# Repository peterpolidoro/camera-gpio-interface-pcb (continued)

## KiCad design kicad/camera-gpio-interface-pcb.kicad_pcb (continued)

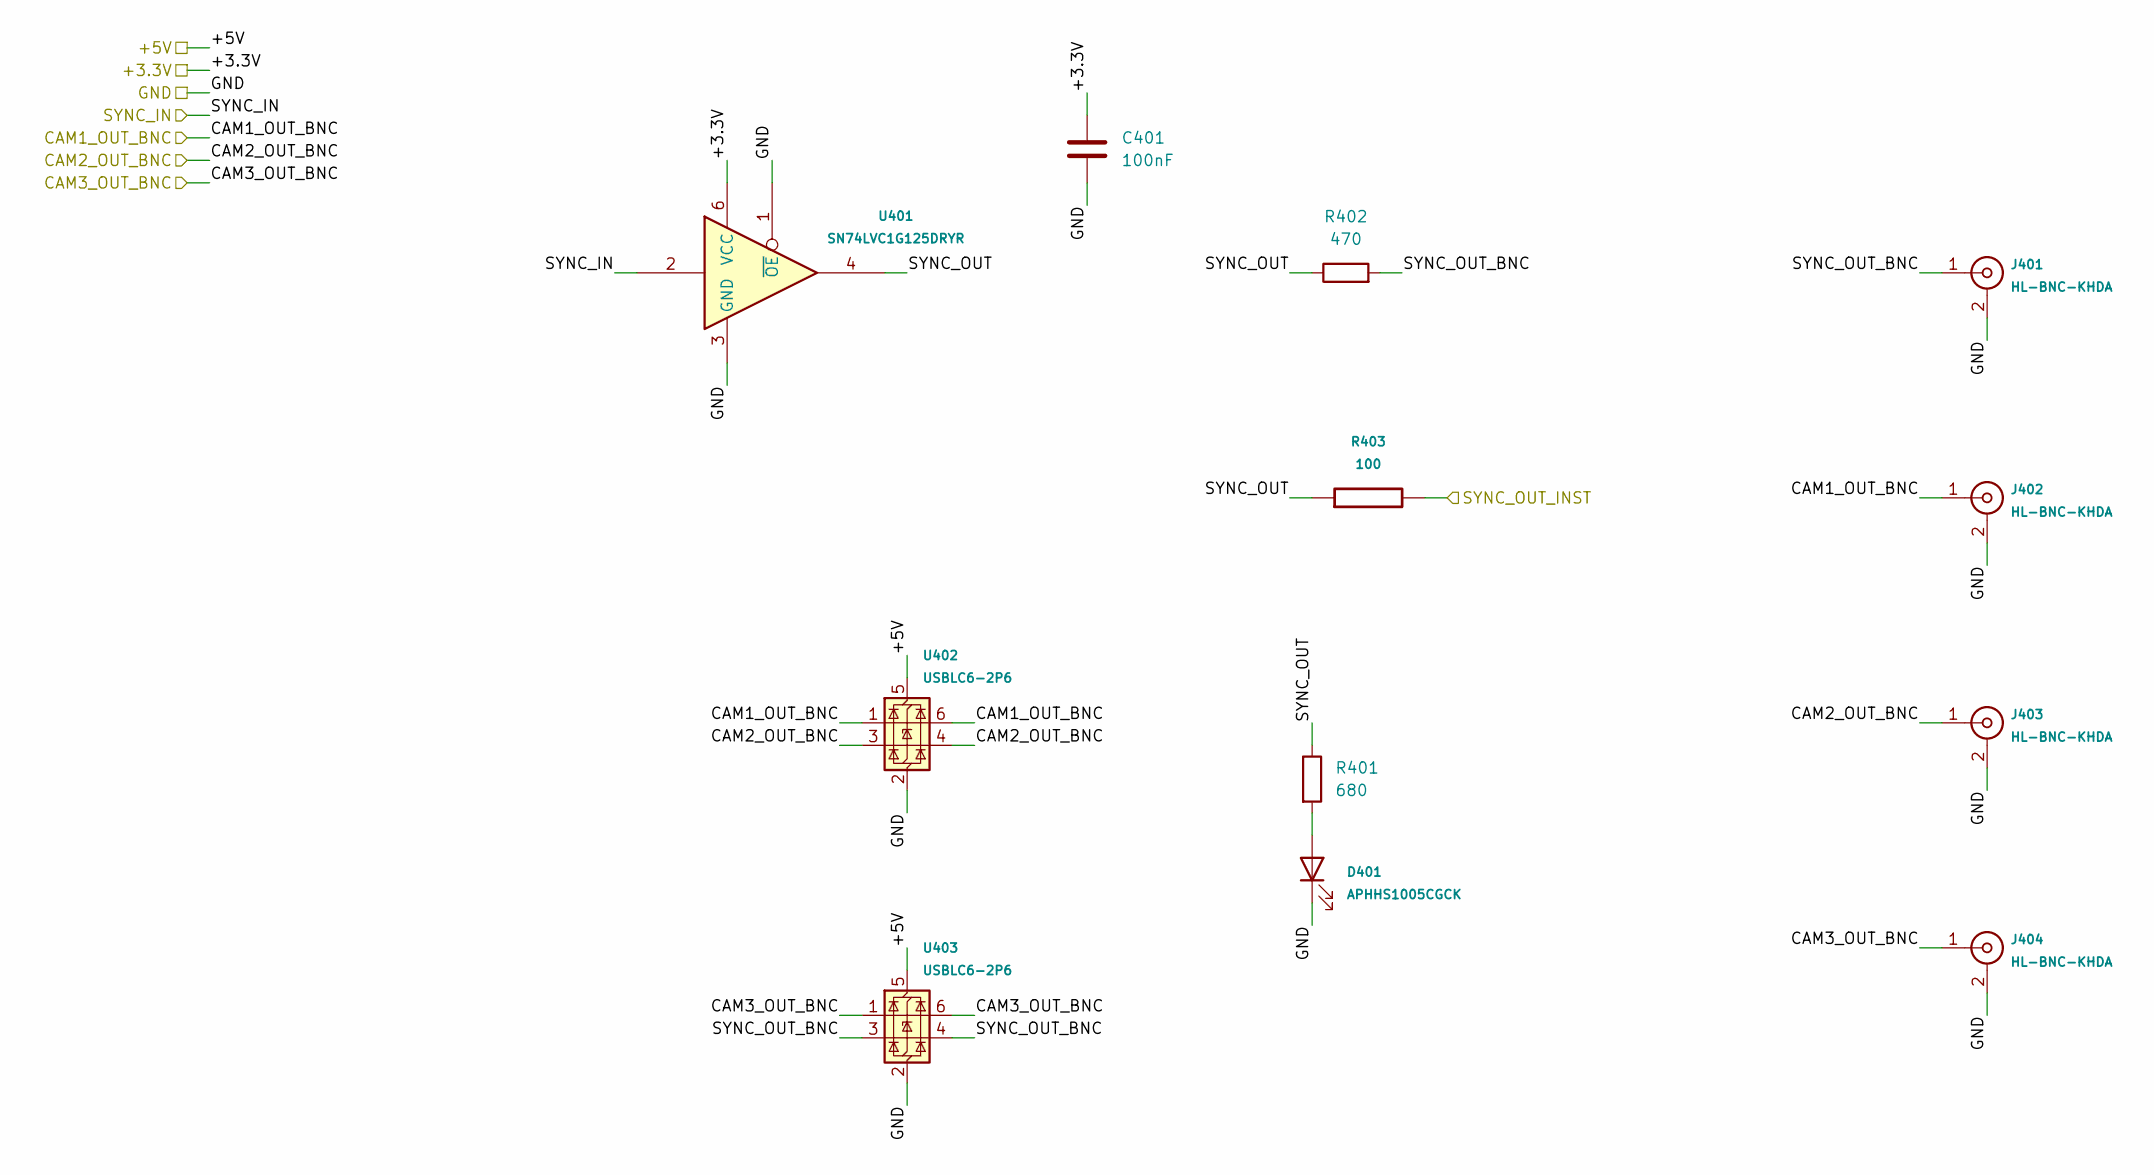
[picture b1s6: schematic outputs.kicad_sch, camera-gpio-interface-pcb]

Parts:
C401: 100nF; C_0402_1005Metric; PartID sym_orb_weaver_passives_c_0_1uf_100v_04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
D401: APHHS1005CGCK; LED_0402-1005_KNB; PartID sym_orb_weaver_misc_led_knb_20ma_grn_2_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
J401, J402, J403, J404: HL-BNC-KHDA; CONN_BNC_HL-BNC-KHDA; PartID sym_orb_weaver_connectors_conn_coaxial_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
R401: 680; R_0402_1005Metric; PartID mpn_rc0402fr_07680rl_0402
R402: 470; R_0603_1608Metric; PartID mpn_0603waf4700t5e_0603
R403: 100; R_0402_1005Metric; PartID sym_orb_weaver_passives_r_100_0402
U401: SN74LVC1G125DRYR; DRY6; PartID sym_orb_weaver_misc_buffer_74lvc1g125dr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
U402, U403: USBLC6-2P6; USBLC6-2P6_SOT-666; PartID mpn_usblc6_2p6_sot_666_6

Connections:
/+3.3V: C401.1, U401.6 (VCC); also elsewhere on the board
/+5V: U402.5 (VBUS), U403.5 (VBUS); also elsewhere on the board
/CAM1_OUT_BNC: J402.1 (Signal), U402.1 (I/O1), U402.6 (I/O1); also elsewhere on the board
/CAM2_OUT_BNC: J403.1 (Signal), U402.3 (I/O2), U402.4 (I/O2); also elsewhere on the board
/CAM3_OUT_BNC: J404.1 (Signal), U403.1 (I/O1), U403.6 (I/O1); also elsewhere on the board
/GND: C401.2, D401.1 (K), J401.2 (Shield), J402.2 (Shield), J403.2 (Shield), J404.2 (Shield), U401.1 (~OE), U401.3 (GND), U402.2 (GND), U403.2 (GND); also elsewhere on the board
/SYNC_IN: U401.2; also elsewhere on the board
/SYNC_OUT_INST: R403.2; also elsewhere on the board
/outputs/SYNC_OUT: R401.1, R402.1, R403.1, U401.4
/outputs/SYNC_OUT_BNC: J401.1 (Signal), R402.2, U403.3 (I/O2), U403.4 (I/O2)
unnamed: D401.2 (A), R401.2

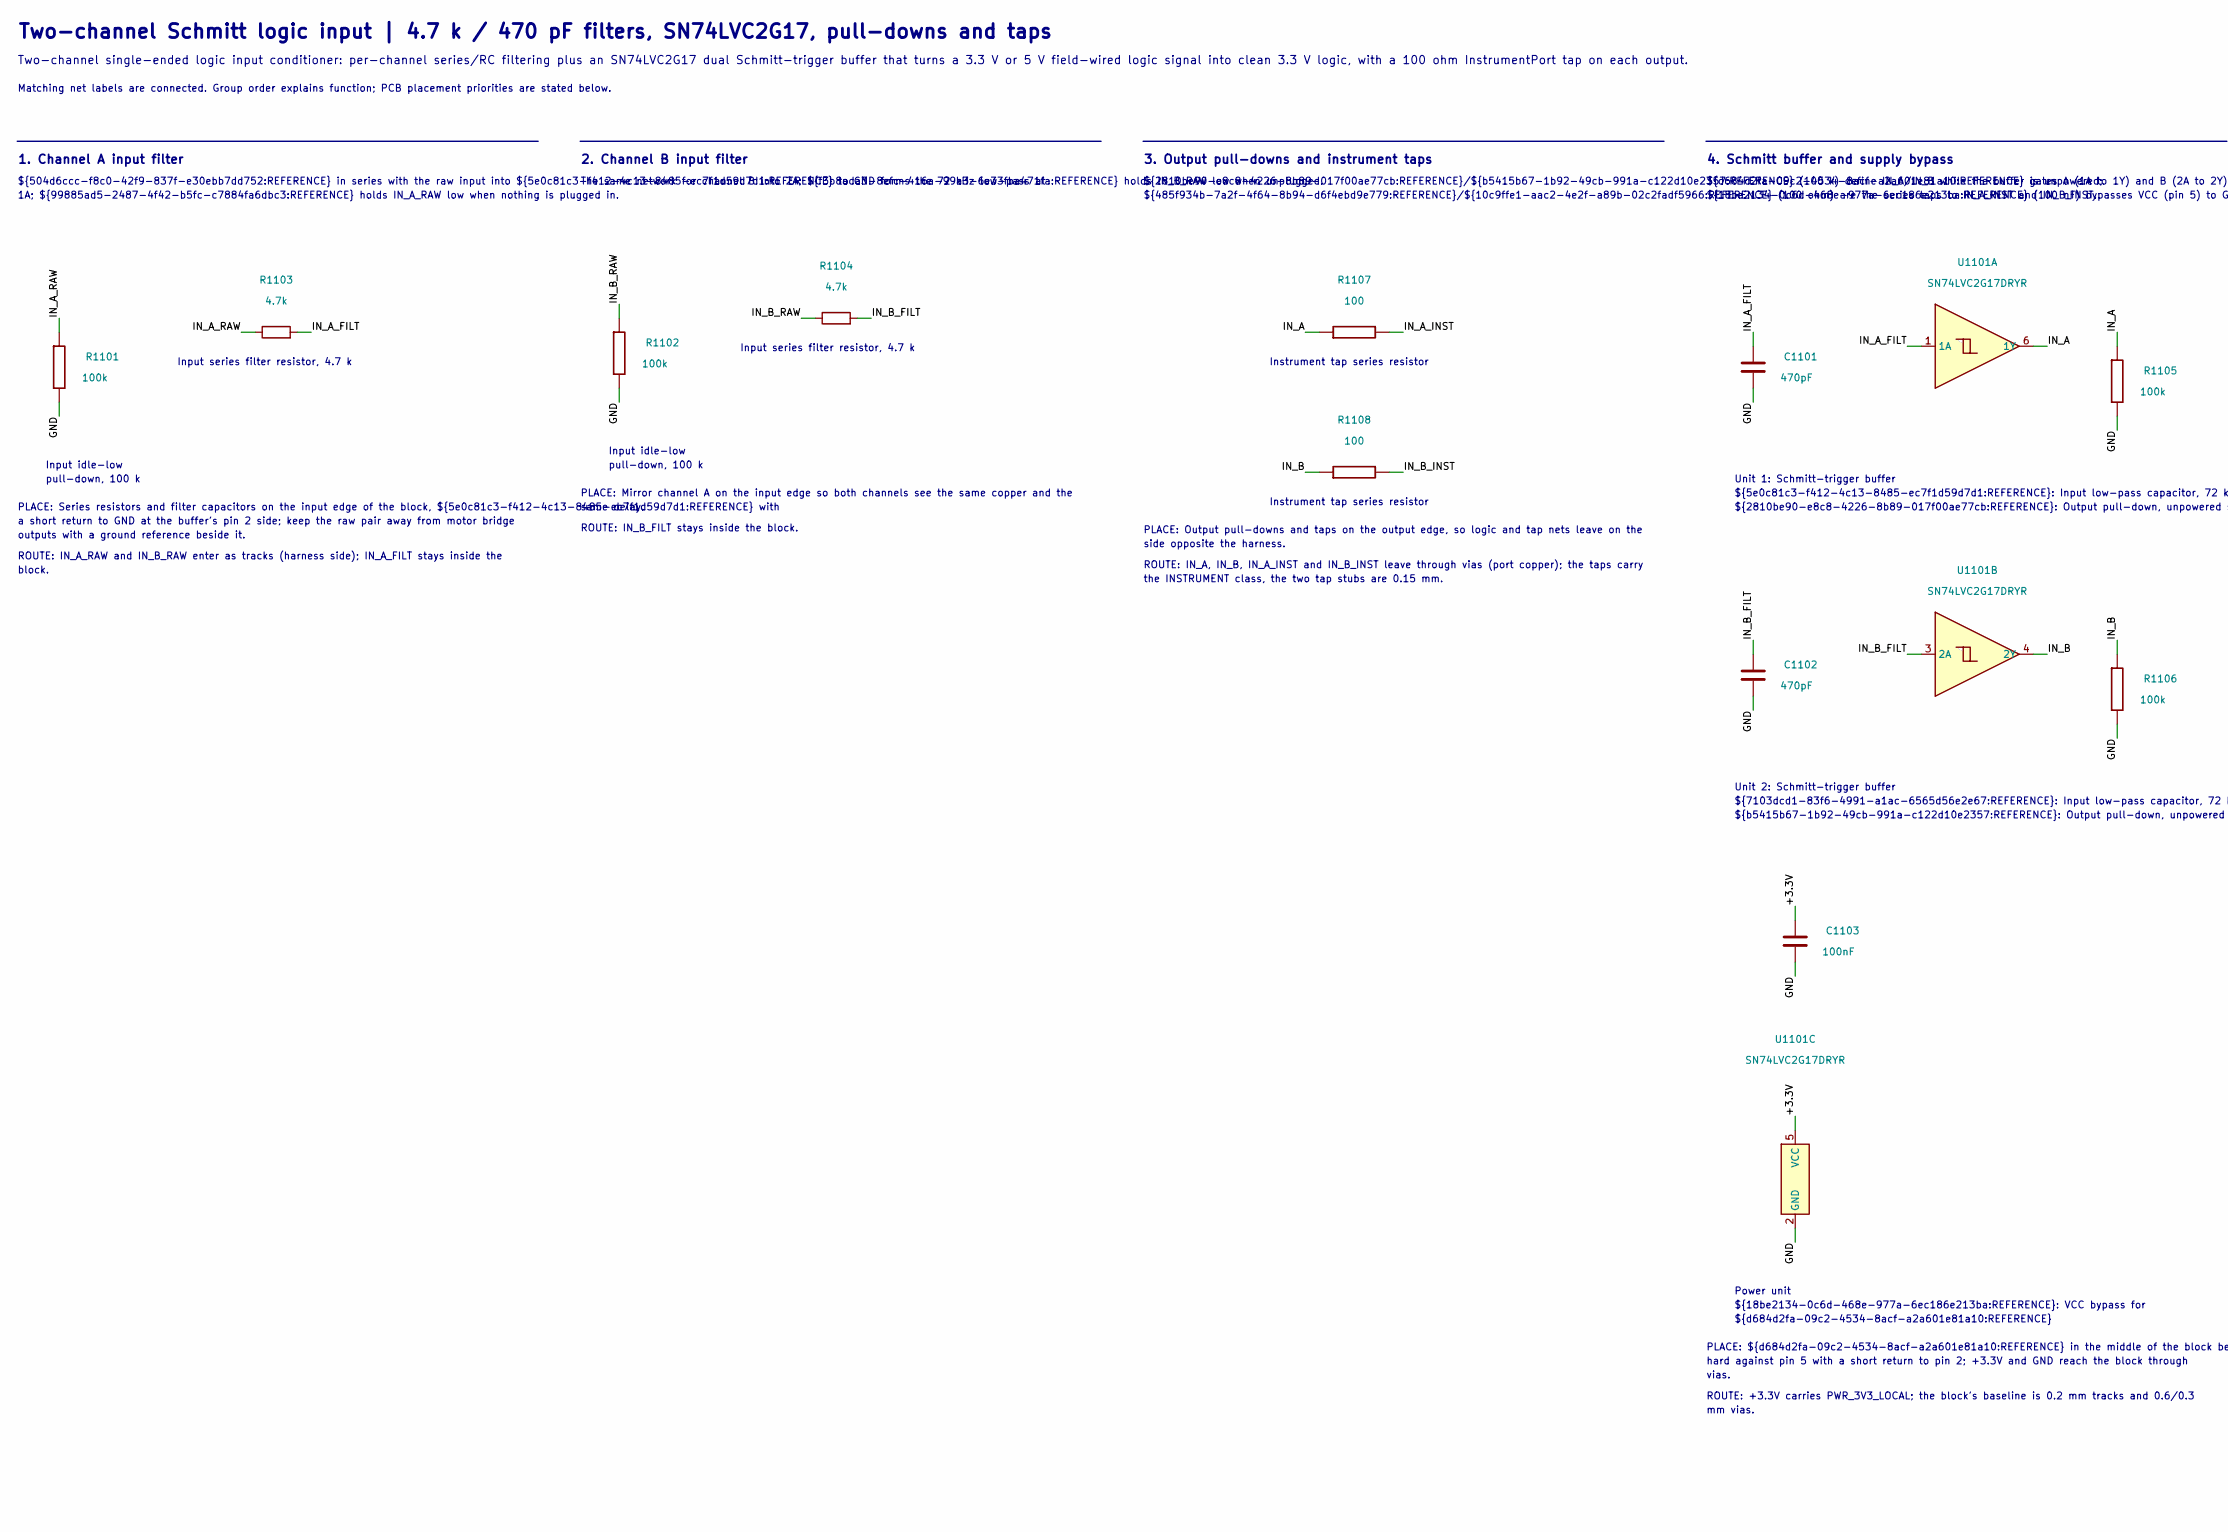
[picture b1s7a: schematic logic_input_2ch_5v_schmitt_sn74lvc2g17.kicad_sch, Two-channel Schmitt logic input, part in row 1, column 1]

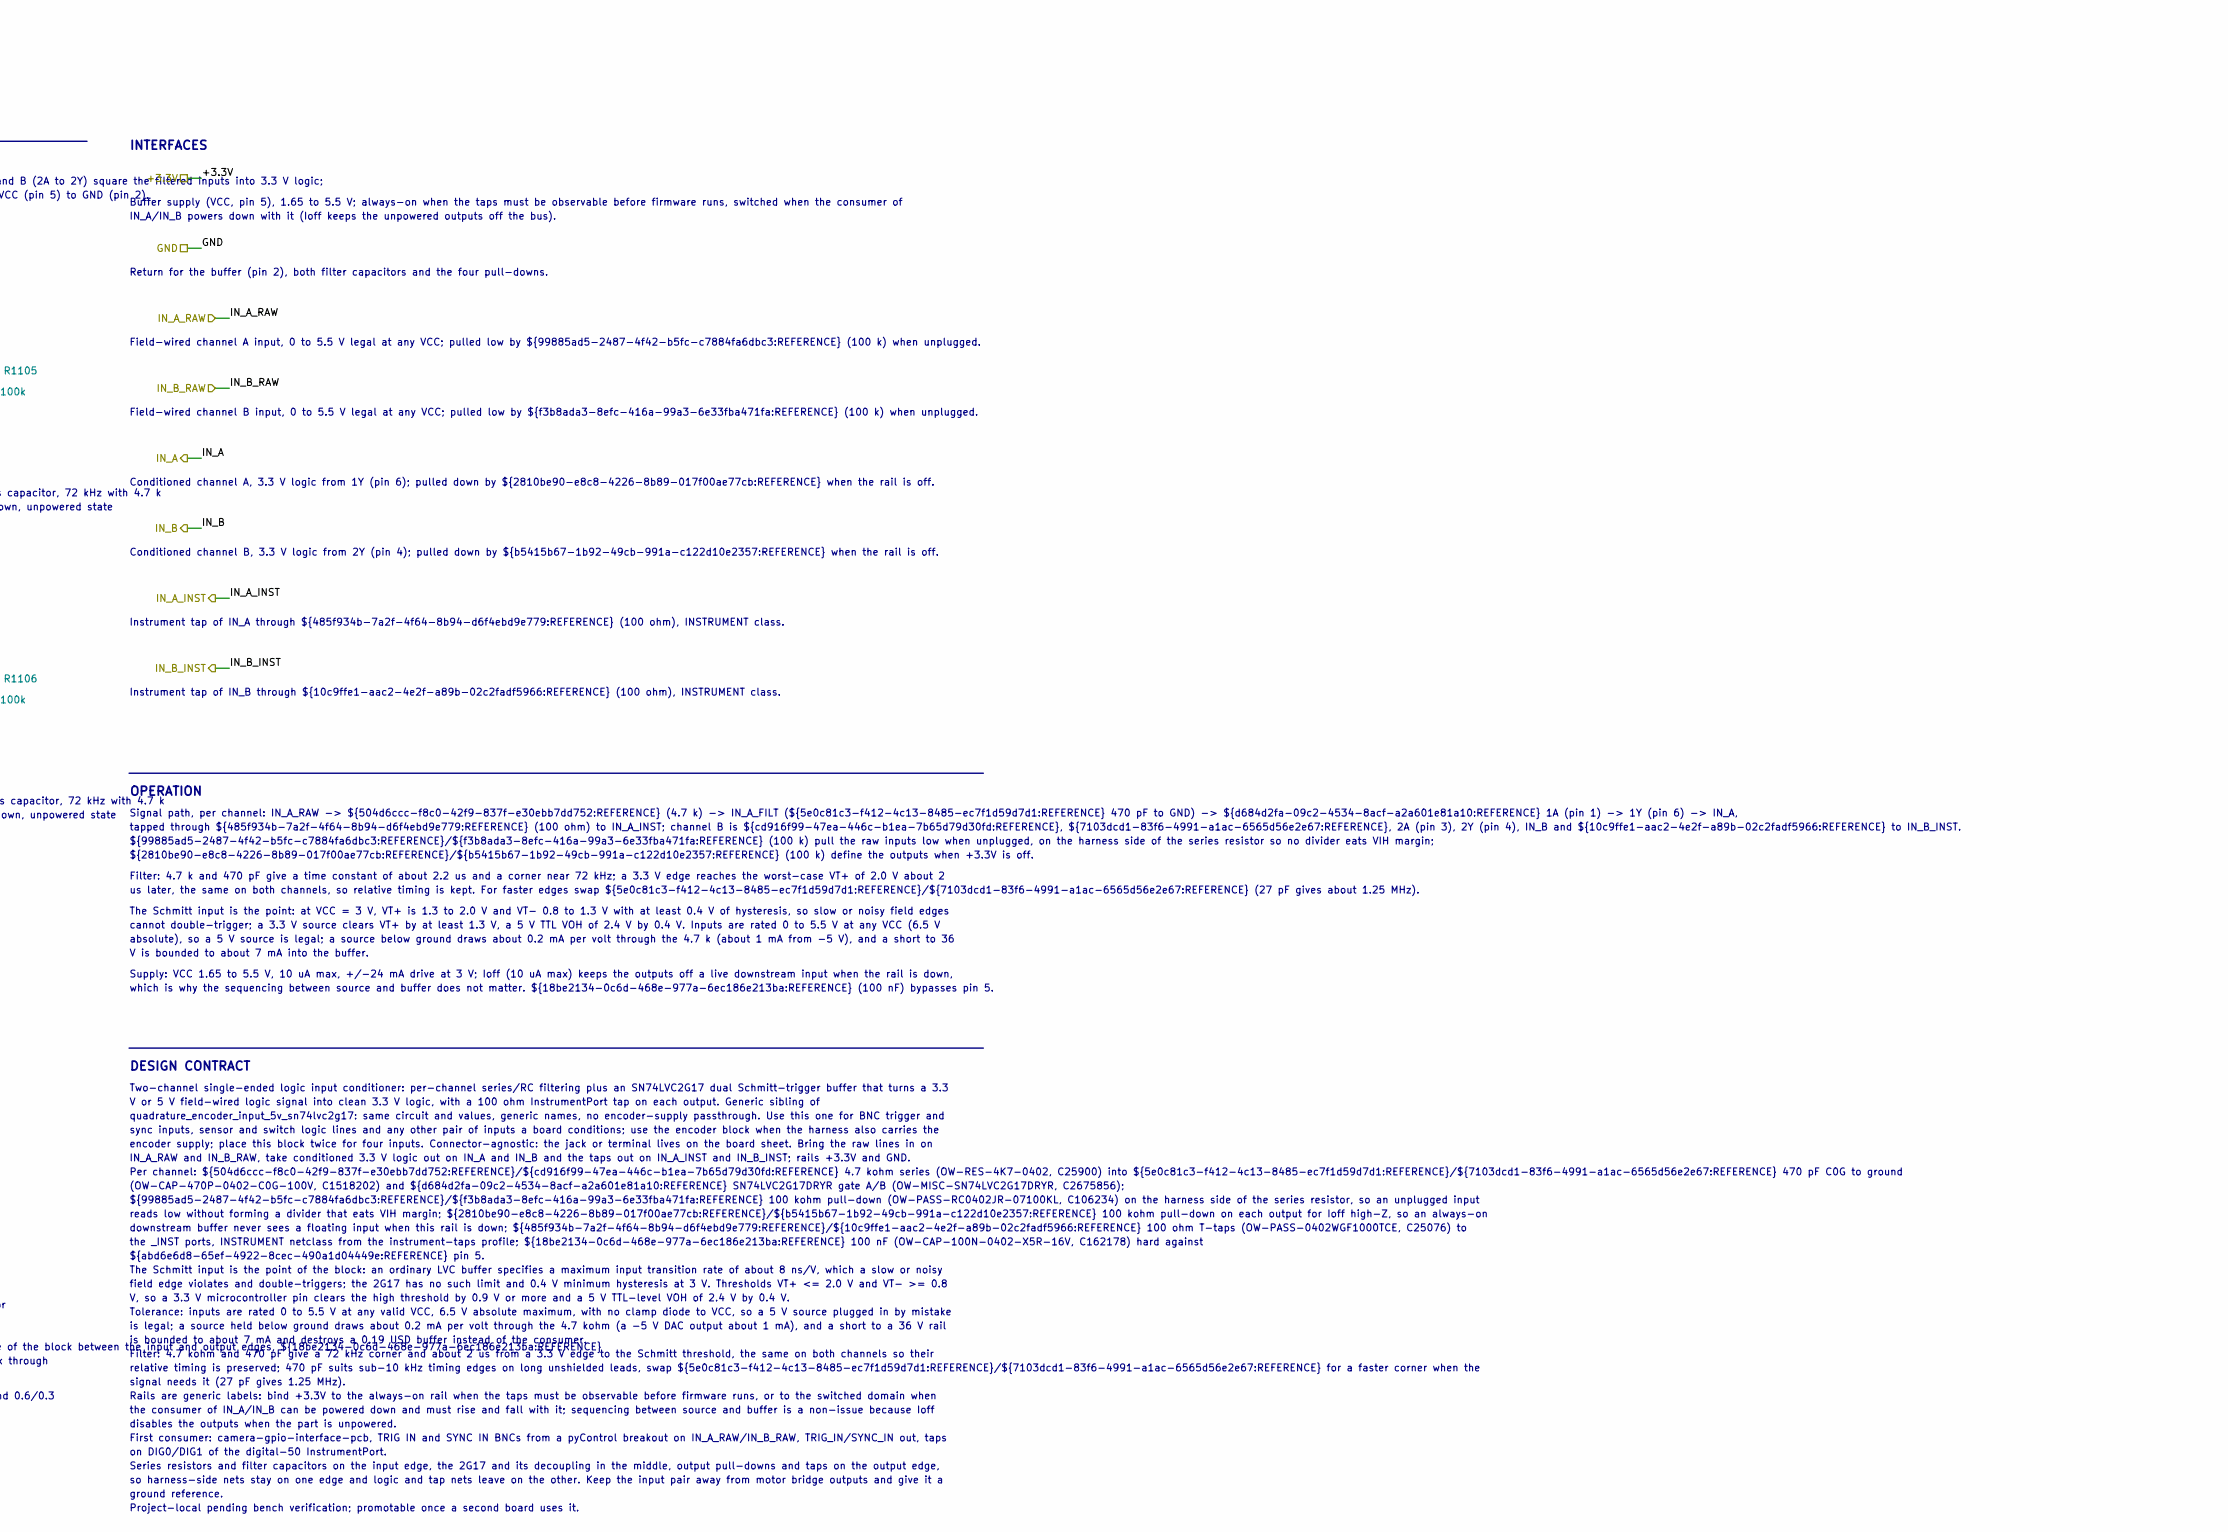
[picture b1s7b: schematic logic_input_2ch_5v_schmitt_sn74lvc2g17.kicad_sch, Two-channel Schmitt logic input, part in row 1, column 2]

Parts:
C1101, C1102: 470pF; C_0402_1005Metric; PartID mpn_grm1555c2a471je01d_0402
C1103: 100nF; C_0402_1005Metric; PartID sym_orb_weaver_passives_c_0_1uf_100v_04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
R1101, R1102, R1105, R1106: 100k; R_0402_1005Metric; PartID sym_orb_weaver_passives_r_100k_0402
R1103, R1104: 4.7k; R_0402_1005Metric; PartID sym_orb_weaver_passives_r_4_7k_0402
R1107, R1108: 100; R_0402_1005Metric; PartID sym_orb_weaver_passives_r_100_0402
U1101: SN74LVC2G17DRYR; DRY6; PartID sym_orb_weaver_misc_buffer_74lvc2g17dryr

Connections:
/+3.3V: C1103.1, U1101.5 (VCC); also elsewhere on the board
/GND: C1101.2, C1102.2, C1103.2, R1101.2, R1102.2, R1105.2, R1106.2, U1101.2 (GND); also elsewhere on the board
/SYNC_IN: R1106.1, R1108.1, U1101.4 (2Y); also elsewhere on the board
/SYNC_IN_INST: R1108.2; also elsewhere on the board
/TRIG_IN: R1105.1, R1107.1, U1101.6 (1Y); also elsewhere on the board
/TRIG_IN_INST: R1107.2; also elsewhere on the board
/inputs/SYNC_RAW: R1102.1, R1104.1; also elsewhere on the board
/inputs/TRIG_RAW: R1101.1, R1103.1; also elsewhere on the board
/inputs/logic_input_2ch_5v_schmitt_sn74lvc2g17/IN_A_FILT: C1101.1, R1103.2, U1101.1 (1A)
/inputs/logic_input_2ch_5v_schmitt_sn74lvc2g17/IN_B_FILT: C1102.1, R1104.2, U1101.3 (2A)

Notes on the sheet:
Two-channel Schmitt logic input | 4.7 k / 470 pF filters, SN74LVC2G17, pull-downs and taps
Two-channel single-ended logic input conditioner: per-channel series/RC filtering plus an SN74LVC2G17 dual Schmitt-trigger buffer that turns a 3.3 V or 5 V field-wired logic signal into clean 3.3 V logic, with a 100 ohm InstrumentPort tap on each output.
Matching net labels are connected. Group order explains function; PCB placement priorities are stated below.
1. Channel A input filter
${504d6ccc-f8c0-42f9-837f-e30ebb7dd752:REFERENCE} in series with the raw input into ${5e0c81c3-f412-4c13-8485-ec7f1d59d7d1:REFERENCE} to GND forms the 72 kHz low-pass at
1A; ${99885ad5-2487-4f42-b5fc-c7884fa6dbc3:REFERENCE} holds IN_A_RAW low when nothing is plugged in.
Input series filter resistor, 4.7 k
Input idle-low
pull-down, 100 k
PLACE: Series resistors and filter capacitors on the input edge of the block, ${5e0c81c3-f412-4c13-8485-ec7f1d59d7d1:REFERENCE} with
a short return to GND at the buffer's pin 2 side; keep the raw pair away from motor bridge
outputs with a ground reference beside it.
ROUTE: IN_A_RAW and IN_B_RAW enter as tracks (harness side); IN_A_FILT stays inside the
block.
2. Channel B input filter
The same network for channel B into 2A; ${f3b8ada3-8efc-416a-99a3-6e33fba471fa:REFERENCE} holds IN_B_RAW low when unplugged.
PLACE: Mirror channel A on the input edge so both channels see the same copper and the
same delay.
ROUTE: IN_B_FILT stays inside the block.
3. Output pull-downs and instrument taps
${2810be90-e8c8-4226-8b89-017f00ae77cb:REFERENCE}/${b5415b67-1b92-49cb-991a-c122d10e2357:REFERENCE} (100 k) define IN_A/IN_B while the buffer is unpowered;
${485f934b-7a2f-4f64-8b94-d6f4ebd9e779:REFERENCE}/${10c9ffe1-aac2-4e2f-a89b-02c2fadf5966:REFERENCE} (100 ohm) are the series taps to IN_A_INST and IN_B_INST.
Instrument tap series resistor
PLACE: Output pull-downs and taps on the output edge, so logic and tap nets leave on the
side opposite the harness.
ROUTE: IN_A, IN_B, IN_A_INST and IN_B_INST leave through vias (port copper); the taps carry
the INSTRUMENT class, the two tap stubs are 0.15 mm.
4. Schmitt buffer and supply bypass
${d684d2fa-09c2-4534-8acf-a2a601e81a10:REFERENCE} gates A (1A to 1Y) and B (2A to 2Y) square the filtered inputs into 3.3 V logic;
${18be2134-0c6d-468e-977a-6ec186e213ba:REFERENCE} (100 nF) bypasses VCC (pin 5) to GND (pin 2).
Unit 1: Schmitt-trigger buffer
${5e0c81c3-f412-4c13-8485-ec7f1d59d7d1:REFERENCE}: Input low-pass capacitor, 72 kHz with 4.7 k
${2810be90-e8c8-4226-8b89-017f00ae77cb:REFERENCE}: Output pull-down, unpowered state
Unit 2: Schmitt-trigger buffer
${7103dcd1-83f6-4991-a1ac-6565d56e2e67:REFERENCE}: Input low-pass capacitor, 72 kHz with 4.7 k
${b5415b67-1b92-49cb-991a-c122d10e2357:REFERENCE}: Output pull-down, unpowered state
Power unit
${18be2134-0c6d-468e-977a-6ec186e213ba:REFERENCE}: VCC bypass for
${d684d2fa-09c2-4534-8acf-a2a601e81a10:REFERENCE}
PLACE: ${d684d2fa-09c2-4534-8acf-a2a601e81a10:REFERENCE} in the middle of the block between the input and output edges, ${18be2134-0c6d-468e-977a-6ec186e213ba:REFERENCE}

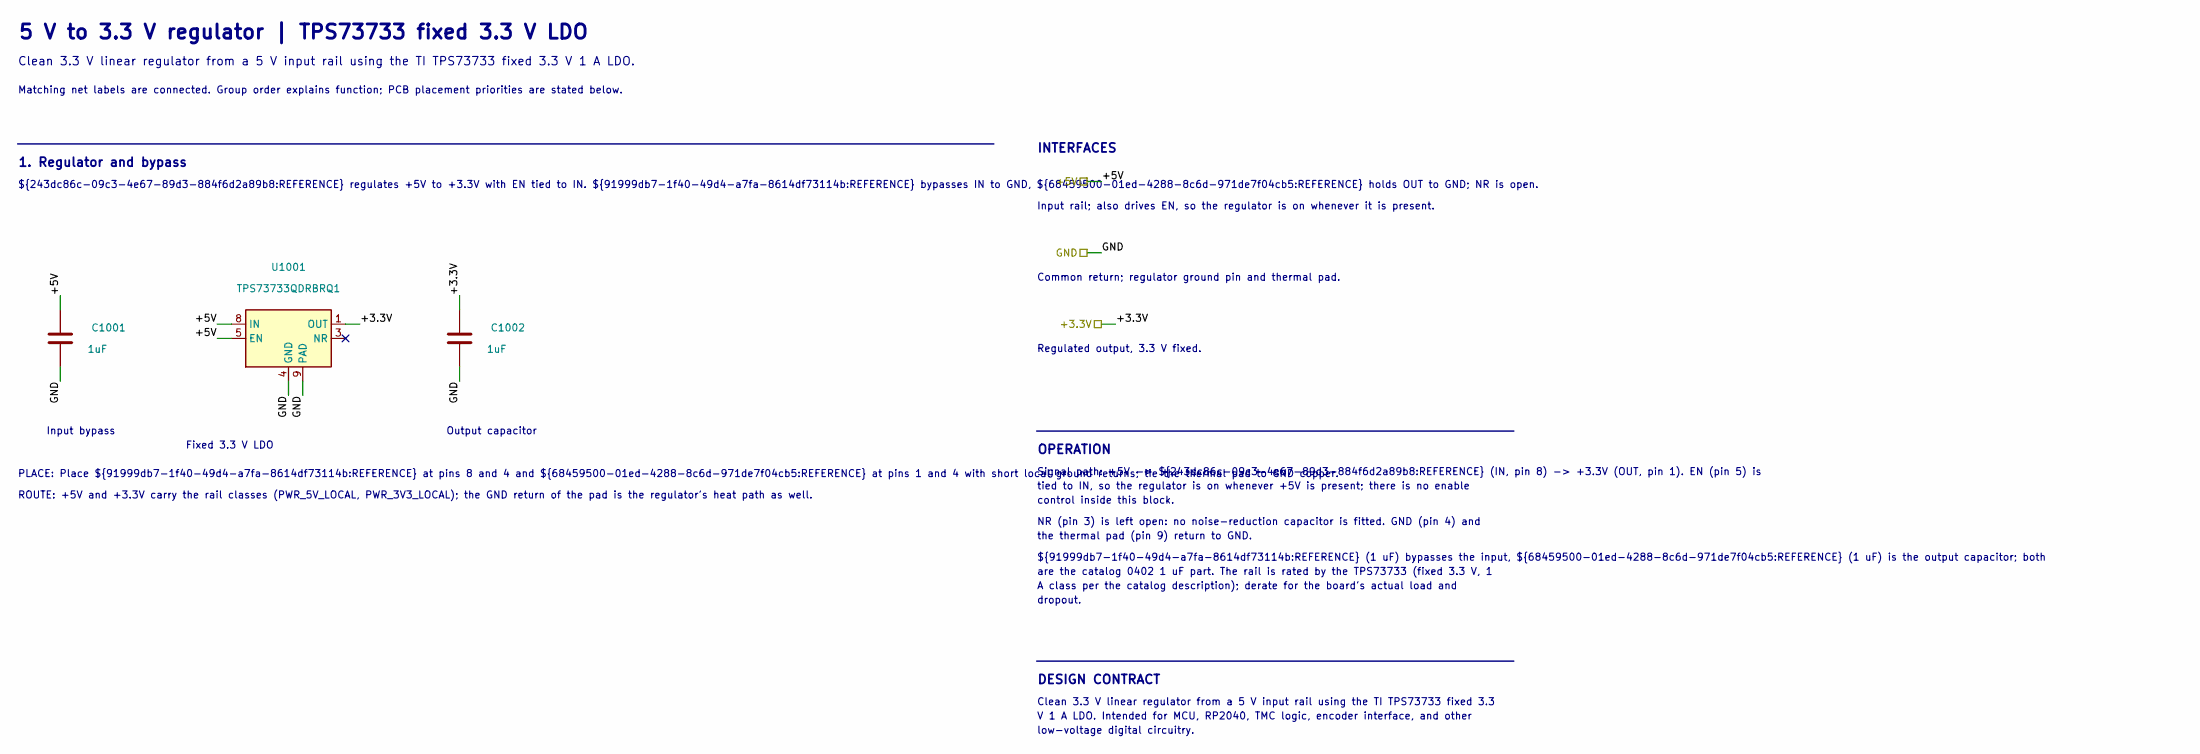
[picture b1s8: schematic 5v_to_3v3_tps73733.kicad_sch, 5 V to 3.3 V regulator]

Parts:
C1001, C1002: 1uF; C_0402_1005Metric; PartID sym_orb_weaver_passives_c_1uf_35v_0402
U1001: TPS73733QDRBRQ1; TPS737Q1; PartID sym_orb_weaver_power_regulator_linear_3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

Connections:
/+3.3V: C1002.1, U1001.1 (OUT); also elsewhere on the board
/+5V: C1001.1, U1001.5 (EN), U1001.8 (IN); also elsewhere on the board
/GND: C1001.2, C1002.2, U1001.4 (GND), U1001.9 (PAD); also elsewhere on the board

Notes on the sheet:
5 V to 3.3 V regulator | TPS73733 fixed 3.3 V LDO
Clean 3.3 V linear regulator from a 5 V input rail using the TI TPS73733 fixed 3.3 V 1 A LDO.
Matching net labels are connected. Group order explains function; PCB placement priorities are stated below.
1. Regulator and bypass
${243dc86c-09c3-4e67-89d3-884f6d2a89b8:REFERENCE} regulates +5V to +3.3V with EN tied to IN. ${91999db7-1f40-49d4-a7fa-8614df73114b:REFERENCE} bypasses IN to GND, ${68459500-01ed-4288-8c6d-971de7f04cb5:REFERENCE} holds OUT to GND; NR is open.
Input bypass
Fixed 3.3 V LDO
Output capacitor
PLACE: Place ${91999db7-1f40-49d4-a7fa-8614df73114b:REFERENCE} at pins 8 and 4 and ${68459500-01ed-4288-8c6d-971de7f04cb5:REFERENCE} at pins 1 and 4 with short local ground returns; tie the thermal pad to GND copper.
ROUTE: +5V and +3.3V carry the rail classes (PWR_5V_LOCAL, PWR_3V3_LOCAL); the GND return of the pad is the regulator's heat path as well.
INTERFACES
Input rail; also drives EN, so the regulator is on whenever it is present.
Common return; regulator ground pin and thermal pad.
Regulated output, 3.3 V fixed.
OPERATION
Signal path: +5V -> ${243dc86c-09c3-4e67-89d3-884f6d2a89b8:REFERENCE} (IN, pin 8) -> +3.3V (OUT, pin 1). EN (pin 5) is
tied to IN, so the regulator is on whenever +5V is present; there is no enable
control inside this block.
NR (pin 3) is left open: no noise-reduction capacitor is fitted. GND (pin 4) and
the thermal pad (pin 9) return to GND.
${91999db7-1f40-49d4-a7fa-8614df73114b:REFERENCE} (1 uF) bypasses the input, ${68459500-01ed-4288-8c6d-971de7f04cb5:REFERENCE} (1 uF) is the output capacitor; both
are the catalog 0402 1 uF part. The rail is rated by the TPS73733 (fixed 3.3 V, 1
A class per the catalog description); derate for the board's actual load and
dropout.
DESIGN CONTRACT
Clean 3.3 V linear regulator from a 5 V input rail using the TI TPS73733 fixed 3.3
V 1 A LDO. Intended for MCU, RP2040, TMC logic, encoder interface, and other
low-voltage digital circuitry.

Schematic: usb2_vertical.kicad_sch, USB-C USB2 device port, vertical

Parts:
C901: 100nF; C_0402_1005Metric; PartID sym_orb_weaver_passives_c_0_1uf_100v_04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
D901: MBR120VLSFT1G; SOD-123FL; PartID sym_orb_weaver_misc_d_schottky_20v_1a
J901: USB-C; USB_C_Receptacle_GCT_USB4145-03-0070-C_16P_Vertical; PartID sym_orb_weaver_connectors_usb_c_recepta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
R901, R902: 5.1k; R_0402_1005Metric; PartID sym_orb_weaver_passives_r_5_1k_0402
U901: USBLC6-2P6; USBLC6-2P6_SOT-666; PartID mpn_usblc6_2p6_sot_666_6

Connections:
/+5V: D901.1 (K); also elsewhere on the board
/GND: C901.2, J901.A1 (GND), J901.A12 (GND), J901.B1 (GND), J901.B12 (GND), J901.S1 (SHIELD), J901.S2 (SHIELD), J901.S3 (SHIELD), J901.S4 (SHIELD), R901.2, R902.2, U901.2 (GND); also elsewhere on the board
/power/usb2_vertical/CC1: J901.A5 (CC1), R901.1
/power/usb2_vertical/CC2: J901.B5 (CC2), R902.1
/power/usb2_vertical/USB_D+: J901.A6 (D+), J901.B6 (D+), U901.3 (I/O2), U901.4 (I/O2)
/power/usb2_vertical/USB_D-: J901.A7 (D-), J901.B7 (D-), U901.1 (I/O1), U901.6 (I/O1)
/power/usb2_vertical/VBUS: C901.1, D901.2 (A), J901.A4 (VBUS), J901.A9 (VBUS), J901.B4 (VBUS), J901.B9 (VBUS), U901.5 (VBUS)

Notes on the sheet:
USB-C USB2 device port, vertical receptacle | USB4145, USBLC6 clamp, Rd 5.1 k, 5 V diode-OR
USB-C USB2 device-port front end on a VERTICAL, top-entry receptacle: GCT USB4145-03-0070-C, OW-CONN-USB-C-USB2-SMD-VERT, 16P USB2-only, SMT contacts plus four through-hole shell legs, 7.46 mm tall.
Matching net labels are connected. Group order explains function; PCB placement priorities are stated below.
1. Receptacle and ESD clamp
${209f383d-7927-4c04-b30a-21fe2c8eb9bb:REFERENCE} brings VBUS, GND, D+/D-, CC1/CC2 and the shell onto the board; ${a93e9f9a-5a6f-4043-8a0b-cad9a8361e7e:REFERENCE} clamps USB_D+, USB_D- and VBUS to GND right at the receptacle. ${7d317996-fe5e-4d1c-afb9-8653c242779c:REFERENCE} holds the raw VBUS node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
the clamp; ${80f6a5a7-fb59-4c71-91f3-2d3c27fa892a:REFERENCE} passes VBUS to +5V_USB and blocks the other 5 V source from feeding back into the host.
ESD clamp on D+, D- and VBUS
${7d317996-fe5e-4d1c-afb9-8653c242779c:REFERENCE}: VBUS bypass at the clamp
${80f6a5a7-fb59-4c71-91f3-2d3c27fa892a:REFERENCE}: Diode-OR Schottky
usb-connector
PLACE: Place ${a93e9f9a-5a6f-4043-8a0b-cad9a8361e7e:REFERENCE} hard against ${209f383d-7927-4c04-b30a-21fe2c8eb9bb:REFERENCE} with a ground via at its pin 2; route each data line in one I/O pad and out the other.
PLACE: Place ${209f383d-7927-4c04-b30a-21fe2c8eb9bb:REFERENCE}'s four shell-leg holes and two locator pegs before pouring GND or routing the port; the part does not seat without them.
PLACE: Place ${7d317996-fe5e-4d1c-afb9-8653c242779c:REFERENCE} between ${a93e9f9a-5a6f-4043-8a0b-cad9a8361e7e:REFERENCE} pin 5 and the GND via; ${80f6a5a7-fb59-4c71-91f3-2d3c27fa892a:REFERENCE} sits where +5V_USB leaves the block at its port via.
ROUTE: USB_D+ and USB_D- are the USB_HS pair: equal length, coupled at the class gap, brought to the block boundary already coupled.
ROUTE: Jump one leg of each pair once at the body centre for the A/B tie; the 0.3 mm gap at the outer contacts is unroutable.
ROUTE: VBUS and +5V_USB are Default-class rails for the port's 5 V budget; +5V_USB is picked up at the port via by the placing board.
2. CC sink declaration
${e0574d6f-c3cf-4023-bcca-2b89f01980b8:REFERENCE} and ${e9b764a5-f224-4026-a384-e54737094fce:REFERENCE} (5.1 k) pull CC1 and CC2 to GND: the port presents itself as a sink; nothing reads the source's advertisement.
CC Rd sink pulldowns
PLACE: Keep ${e0574d6f-c3cf-4023-bcca-2b89f01980b8:REFERENCE} at A5 and ${e9b764a5-f224-4026-a384-e54737094fce:REFERENCE} at B5 with short returns; no other load on CC1 or CC2.
ROUTE: CC1 and CC2 are Default-class local nets that end at the resistors.
3. Power drive declarations
These nets have an explicit ERC power source declaration.
Power driven: VBUS
INTERFACES
Raw bus 5 V, ${209f383d-7927-4c04-b30a-21fe2c8eb9bb:REFERENCE} A4, A9, B4, B9; bypassed by ${7d317996-fe5e-4d1c-afb9-8653c242779c:REFERENCE}, the clamp's reference.
VBUS through ${80f6a5a7-fb59-4c71-91f3-2d3c27fa892a:REFERENCE} (Schottky, about 0.3 V drop) for diode-ORing with +5V_PYC.
USB ground: ${209f383d-7927-4c04-b30a-21fe2c8eb9bb:REFERENCE} A1, B1, A12, B12 and shell S1 to S4; clamp and Rd return.
USB 2.0 D+, ${209f383d-7927-4c04-b30a-21fe2c8eb9bb:REFERENCE} A6 and B6, after the ${a93e9f9a-5a6f-4043-8a0b-cad9a8361e7e:REFERENCE} clamp; USB_HS pair with USB_D-.
USB 2.0 D-, ${209f383d-7927-4c04-b30a-21fe2c8eb9bb:REFERENCE} A7 and B7, after the ${a93e9f9a-5a6f-4043-8a0b-cad9a8361e7e:REFERENCE} clamp; USB_HS pair with USB_D+.
INTERNAL NETS
CC1: Configuration channel for one plug orientation, ${209f383d-7927-4c04-b30a-21fe2c8eb9bb:REFERENCE} A5 to ${e0574d6f-c3cf-4023-bcca-2b89f01980b8:REFERENCE} (Rd, 5.1 k to GND); nothing reads it.
CC2: Configuration channel for the other orientation, ${209f383d-7927-4c04-b30a-21fe2c8eb9bb:REFERENCE} B5 to ${e9b764a5-f224-4026-a384-e54737094fce:REFERENCE} (Rd, 5.1 k to GND); nothing reads it.
OPERATION
Signal path: ${209f383d-7927-4c04-b30a-21fe2c8eb9bb:REFERENCE} D+ (A6, B6) and D- (A7, B7) pass ${a93e9f9a-5a6f-4043-8a0b-cad9a8361e7e:REFERENCE}'s I/O pads to USB_D+ and USB_D-; both receptacle rows are tied so either plug
orientation works. SBU1 and SBU2 (A8, B8) are no-connect: USB2 only, for an RP2040-class device controller.
CC: ${e0574d6f-c3cf-4023-bcca-2b89f01980b8:REFERENCE} on CC1 (A5) and ${e9b764a5-f224-4026-a384-e54737094fce:REFERENCE} on CC2 (B5), 5.1 k to GND, declare a UFP (sink). Nothing reads the CC level, so budget the load against a
default-power source unless the host is known to advertise 1.5 A or 3 A.
ESD: ${a93e9f9a-5a6f-4043-8a0b-cad9a8361e7e:REFERENCE} (USBLC6-2P6) clamps D+, D- and VBUS: 3.5 pF max per line, 1.7 pF max line to line, 6 V minimum VBUS breakdown, 12 V typical
clamp at 1 A 8/20 us, IEC 61000-4-2 level 4 (15 kV air and contact). Clamp performance is set by connection inductance: pin 2 to a ground via,

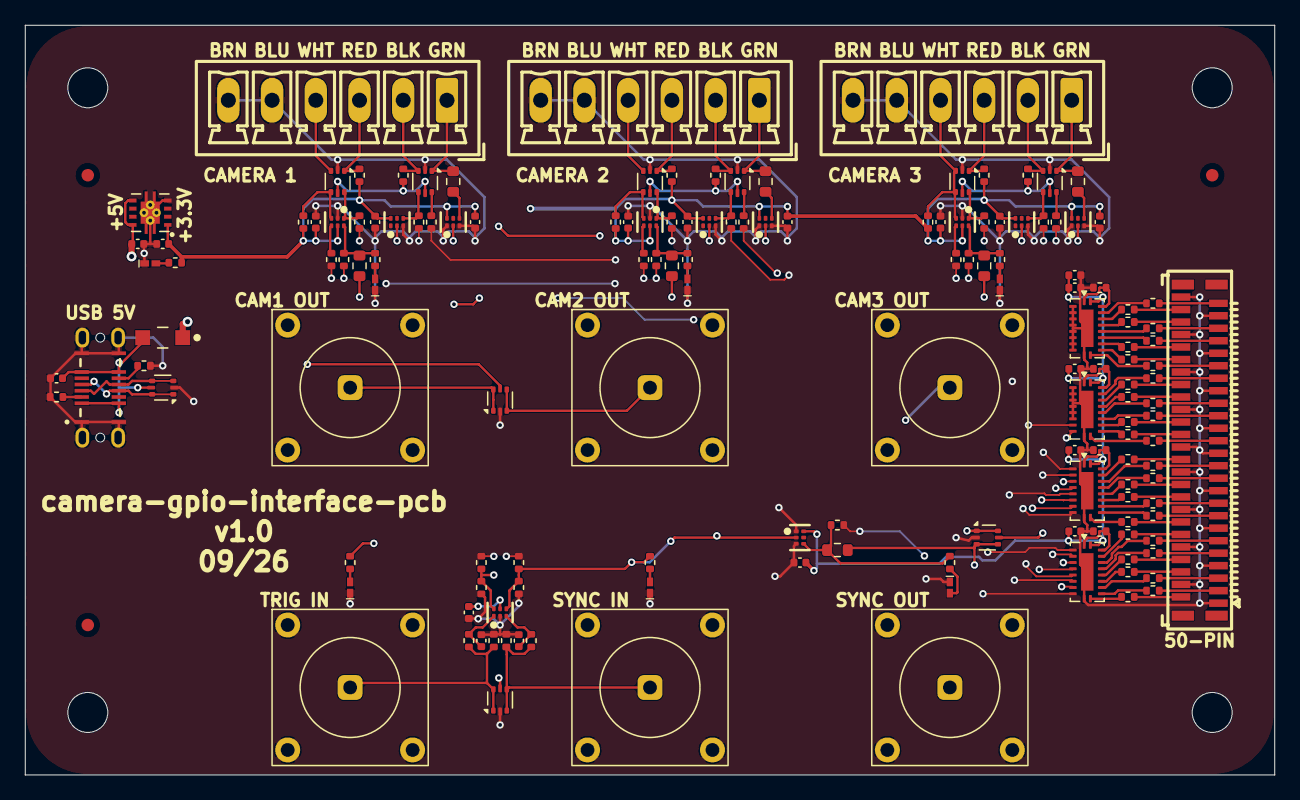
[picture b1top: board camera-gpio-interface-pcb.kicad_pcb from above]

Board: 4 copper layers, 100.0 x 60.0 mm, 158 parts (0 on the bottom side), 133 nets.
